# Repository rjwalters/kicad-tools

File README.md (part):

# kicad-tools

**Tools for AI agents to work with KiCad projects.**

🌐 **Live demo gallery: [kicad-tools.org](https://kicad-tools.org)** — explore example boards built end-to-end by these tools, with 2D/3D renders, routing & manufacturing metrics, downloadable fabrication packages, and an interactive in-browser PCB viewer.

This project provides standalone Python tools that enable AI agents (LLMs, autonomous coding assistants, etc.) to parse, analyze, and manipulate KiCad schematic and PCB files programmatically. All tools output machine-readable JSON and require no running KiCad instance.

## Why Agent-Focused?

Traditional EDA tools require GUIs and manual interaction. `kicad-tools` bridges the gap by providing:

- **Structured data access** - Parse KiCad files into clean Python objects
- **Machine-readable output** - Analysis and query commands offer JSON output; check each command’s `--help` for supported formats
- **Programmatic modification** - Edit schematics and PCBs without a GUI
- **LLM reasoning interface** - Purpose-built module for LLM-driven PCB layout decisions

Whether you're building an AI assistant that reviews PCB designs, automating DRC checks in CI, or experimenting with LLM-driven routing, these tools provide the foundation.

## Installation

```bash
# Base install (CPU only)
pip install kicad-tools

# With CUDA GPU acceleration (NVIDIA GPUs on Linux/Windows)
pip install kicad-tools[cuda]

# With Metal GPU acceleration (Apple Silicon Macs)
pip install kicad-tools[metal]

# With native C++ router backend
pip install kicad-tools[native]

# With CMA-ES placement optimization (kct optimize-placement / kct build --optimize-placement)
pip install kicad-tools[placement]

# Everything (all optional dependencies)
pip install kicad-tools[all]
```

> The `placement` extra pulls in `cmaes` (and, transitively, `scipy`). It is
> required by `kct optimize-placement` and the placement step of
> `kct build --optimize-placement`; without it those commands exit with a
> clear message naming the extra. The `dev` and `all` extras already include
> it, so `uv sync --extra dev` is sufficient for development.

To check GPU acceleration status:
```bash
kct calibrate --show-gpu
```

### In a board (consumer) repository

The supported setup for a PCB-design repo that depends on kicad-tools is **PyPI
plus a committed `uv.lock`**: `pyproject.toml` carries a lower bound
(`kicad-tools[<extras>]>=X`) and `uv.lock` is the exact pin. Install it, with
the agent skills, CI gates and conventions, from a kicad-tools checkout:

```bash
./scripts/install-kct.sh /path/to/board-repo        # PyPI floor (default; same as --pypi)
./scripts/install-kct.sh --upgrade-workflow /path/to/board-repo  # + weekly upgrade PR
cd /path/to/board-repo && uv lock && uv sync && uv run kct build-native
```

The installer keeps the repo's existing extras and removes any
`[tool.uv.sources]` kicad-tools entry. Re-running it is a no-op when the floor
is already current. `--upgrade-workflow` adds `.github/workflows/kct-upgrade.yml`,
which opens a PR for each new PyPI release; the PR raises the floor, refreshes
`uv.lock` and the vendored files, and lists the release's upgrade notes.
`kct doctor` checks that the vendored files match the installed version.

Git and SHA pins (`--tag vX.Y.Z`, `--rev <sha>`) and local checkouts
(`--path ../kicad-tools`) are escape hatches for short-lived use. If you need
a fix that is not on PyPI yet, ask for a patch release rather than carrying a
SHA pin. Run `./scripts/install-kct.sh --help` for every option.

## Quick Start

### Command Line (`kct`)

```bash
# List symbols in a schematic
kct symbols project.kicad_sch
kct symbols project.kicad_sch --format json

# Trace nets
kct nets project.kicad_sch
kct nets project.kicad_sch --net VCC

# Generate bill of materials
kct bom project.kicad_sch
kct bom project.kicad_sch --format csv --group

# Run ERC (requires kicad-cli)
kct erc project.kicad_sch
kct erc project.kicad_sch --errors-only

# Run DRC with manufacturer rules
kct drc board.kicad_pcb
kct drc board.kicad_pcb --mfr jlcpcb
kct mfr compare  # Compare manufacturer rules
```

### Python API

```python
from kicad_tools import load_schematic, Schematic

# Load and parse a schematic
doc = load_schematic("project.kicad_sch")
sch = Schematic(doc)

# Access symbols
for symbol in sch.symbols:
    print(f"{symbol.reference}: {symbol.value}")

# Access hierarchy
for sheet in sch.sheets:
    print(f"Sheet: {sheet.name}")
```

### PCB Autorouter

```python
from kicad_tools.router import Autorouter, DesignRules

# Configure design rules
rules = DesignRules(
    grid_resolution=0.25,  # mm
    trace_width=0.2,  # mm
    trace_clearance=0.15,  # mm
)

# Create router and add components
router = Autorouter(width=100, height=80, rules=rules)
router.add_component("U1", pads=[{"number": "1", "x": 10, "y": 10, "net": 1}])
router.add_component("U2", pads=[{"number": "1", "x": 20, "y": 10, "net": 1}])

# Route all nets
routes = router.route_all(timeout=30)
print(f"Created {len(routes)} routes")
```

### LLM-Driven PCB Layout

The reasoning module enables LLMs to make strategic PCB layout decisions while tools handle geometric execution:

```python
from kicad_tools import PCBReasoningAgent

# Load board
agent = PCBReasoningAgent.from_pcb("board.kicad_pcb")

# Reasoning loop
while not agent.is_complete():
    # Get state as prompt for LLM
    prompt = agent.get_prompt()

    # Call your LLM (OpenAI, Anthropic, local, etc.)
    command = call_llm(prompt)

    # Execute and get feedback
    result, diagnosis = agent.execute(command)

# Save result
agent.save("board_routed.kicad_pcb")
```

CLI usage:
```bash
# Export state for external LLM
kct reason board.kicad_pcb --export-state

# Interactive mode
kct reason board.kicad_pcb --interactive

# Auto-route priority nets
kct reason board.kicad_pcb --auto-route
```

See `examples/llm-routing/` for complete examples.

### MCP Server for AI Agents

Enable AI assistants like Claude to interact with KiCad designs via the Model Context Protocol:

```bash
# Install with MCP support
pip install "kicad-tools[mcp]"

# Run the MCP server
kct mcp serve
```

Register the server with your agent harness. `kct mcp setup` finds the
absolute `kct` path, merges into the existing config without touching other
servers, and is a no-op when re-run (`--dry-run` previews, `--format json` for
scripts):

```bash
kct mcp setup --client claude-code      # ~/.claude.json via `claude mcp add-json` (default; --scope project for ./.mcp.json)
kct mcp setup --client claude-desktop   # Claude Desktop config
kct mcp setup --client codex            # [mcp_servers.kct] in $CODEX_HOME/config.toml
kct mcp setup --client opencode         # ~/.config/opencode/opencode.json (--project for ./opencode.json)
```

Or configure Claude Desktop by hand (`~/Library/Application Support/Claude/claude_desktop_config.json`):

```json
{
  "mcpServers": {
    "kicad-tools": {
      "command": "python",
      "args": ["-m", "kicad_tools.mcp.server"]
    }
  }
}
```

Available MCP tools:
- **Analysis**: `board_summary`, `get_drc_violations`, `measure_clearance`
- **Export**: `export_gerbers`, `export_bom`, `export_assembly`
- **Placement**: `placement_analyze`, `placement_suggestions`
- **Sessions**: `start_session`, `query_move`, `apply_move`, `commit`, `rollback`
- **Routing**: `route_net`, `route_net_auto`, `get_unrouted_nets`
- **Optimization**: `optimize_placement`, `evaluate_placement`

See `docs/mcp/` for complete documentation.

### Circuit Blocks

Build schematics using reusable, tested circuit blocks:

```python
from kicad_tools.schematic.models import Schematic
from kicad_tools.schematic.blocks import (
    MCUBlock,
    CrystalOscillator,
    LDOBlock,
    USBConnector,
    DebugHeader,
    I2CPullups,
    ResetButton,
)

sch = Schematic("My STM32 Design")

# Add an MCU with bypass capacitors
mcu = MCUBlock(
    sch, x=150, y=100, part="STM32F103C8T6", bypass_caps=["100nF", "100nF", "100nF", "4.7uF"]
)

# Add crystal oscillator
xtal = CrystalOscillator(sch, x=100, y=100, frequency="8MHz", load_caps="20pF")

# Add power supply
ldo = LDOBlock(sch, x=50, y=100, input_voltage=5.0, output_voltage=3.3)

# Add USB connector with ESD protection
usb = USBConnector(sch, x=50, y=150, connector_type="type-c", esd_protection=True)

# Add debug header for programming
debug = DebugHeader(sch, x=200, y=100, interface="swd")

# Add I2C pull-ups
i2c = I2CPullups(sch, x=180, y=150, pullup_value="4.7k")

# Add reset button with debounce
reset = ResetButton(sch, x=120, y=50, debounce_cap="100nF")

# Connect via ports
sch.add_wire(ldo.port("VOUT"), mcu.port("VDD"))
sch.add_wire(xtal.port("OUT"), mcu.port("OSC_IN"))

sch.save()
```

Available blocks:
- **MCUBlock**: Microcontroller with bypass capacitors
- **CrystalOscillator**: Crystal/oscillator with load capacitors
- **LDOBlock**: Linear regulator with input/output capacitors
- **USBConnector**: USB-B/Mini/Micro/Type-C with optional ESD protection
- **DebugHeader**: SWD/JTAG/Tag-Connect programming headers
- **I2CPullups**: I2C bus pull-up resistors with optional filtering
- **ResetButton**: Reset switch with debounce capacitor
- **BarrelJackInput/USBPowerInput/BatteryInput**: Power input circuits
- **LEDIndicator**: Status LED with current-limiting resistor
- **DecouplingCaps**: Decoupling capacitor placement

See `boards/04-stm32-devboard/` for a complete design example.

### Project Workflow

Work with complete KiCad projects using the unified Project class:

```python
from kicad_tools import Project

# Load a KiCad project
project = Project.load("myboard.kicad_pro")

# Cross-reference schematic to PCB
result = project.cross_reference()
print(f"Unplaced components: {result.unplaced}")

# Export manufacturing files
project.export_assembly("output/", manufacturer="jlcpcb")
```

### Progress Callbacks

Monitor long-running operations with progress callbacks:

```python
from kicad_tools import ProgressCallback, ProgressContext
from kicad_tools.router import Autorouter

def on_progress(progress: float, message: str, cancelable: bool) -> bool:
    print(f"{progress * 100:.0f}%: {message}")
    return True  # Return False to cancel

# Use with context manager
with ProgressContext(on_progress):
    router = Autorouter(...)
    router.route_all()  # Progress reported automatically

# Or create JSON-formatted callbacks for automation
from kicad_tools import create_json_callback

callback = create_json_callback()
```

### Parametric Footprint Generators

Create KiCad footprints programmatically with IPC-7351 naming:

```python
from kicad_tools.library import create_soic, create_qfp, create_chip

# Generate SOIC-8 footprint
fp = create_soic(pins=8, pitch=1.27)
fp.save("SOIC-8.kicad_mod")

# Generate LQFP-48
fp = create_qfp(pins=48, pitch=0.5, body_size=7.0)
fp.save("LQFP-48.kicad_mod")

# Generate 0402 chip resistor
fp = create_chip("0402", prefix="R")
fp.save("R_0402.kicad_mod")
```

Available generators: `create_soic`, `create_qfp`, `create_qfn`, `create_sot`, `create_chip`, `create_dip`, `create_pin_header`.

### Symbol Library Management

Create and edit KiCad symbol libraries programmatically:

```python
from kicad_tools.schema.library import SymbolLibrary

# Create a new symbol library
lib = SymbolLibrary.create("myproject.kicad_sym")

# Create a symbol with pins
sym = lib.create_symbol("MyPart")
sym.add_pin("1", "VCC", "power_in", (0, 5.08))
sym.add_pin("2", "GND", "power_in", (0, -5.08))
sym.add_pin("3", "IN", "input", (-7.62, 0))
sym.add_pin("4", "OUT", "output", (7.62, 0))

# Save the library
lib.save()

# Load and edit existing library
lib = SymbolLibrary.load("existing.kicad_sym")
```

### Pure Python DRC

Run design rule checks without requiring kicad-cli:

```bash
# Check against manufacturer rules
kct check board.kicad_pcb --mfr jlcpcb --format json

# Check against a 4-layer rule set with 2 oz outer / 0.5 oz inner copper.
# (A scalar `--copper 2` would also apply 2 oz to inner layers; omit the flag
# when the board declares a stackup.)
kct check board.kicad_pcb --mfr jlcpcb --layers 4 --copper outer=2,inner=0.5
```

Python API:

```python
from kicad_tools.schema.pcb import PCB
from kicad_tools.validate import DRCChecker

pcb = PCB.load("board.kicad_pcb")
checker = DRCChecker(pcb, manufacturer="jlcpcb")
results = checker.check_all()

print(results.summary())
for violation in results:
    print(f"  {violation.rule_id}: {violation.message}")
```

### Placement Optimization

Optimize component placement using physics-based or evolutionary algorithms:

```python
from kicad_tools.optim import PlacementOptimizer, EvolutionaryPlacementOptimizer
from kicad_tools.schema.pcb import PCB

pcb = PCB.load("board.kicad_pcb")

# Physics-based optimization (force-directed)
optimizer = PlacementOptimizer.from_pcb(pcb)
optimizer.run(iterations=1000, dt=0.01)

# Get optimized placements
for comp in optimizer.components:
    print(f"{comp.ref}: ({comp.x:.2f}, {comp.y:.2f}) @ {comp.rotation:.1f}°")

# Evolutionary optimization (genetic algorithm)
evo = EvolutionaryPlacementOptimizer.from_pcb(pcb)
best = evo.optimize(generations=100, population_size=50)

# Hybrid: evolutionary global search + physics refinement
physics_opt = evo.optimize_hybrid(generations=50)
physics_opt.write_to_pcb(pcb)
pcb.save("optimized.kicad_pcb")
```

CLI usage:
```bash
kct placement optimize board.kicad_pcb --iterations 1000
```

### Trace Optimization

Optimize routed traces for shorter paths and fewer vias:

```python
from kicad_tools.router import TraceOptimizer
from kicad_tools.schema.pcb import PCB

pcb = PCB.load("board.kicad_pcb")
optimizer = TraceOptimizer(pcb)
optimizer.optimize()
pcb.save("optimized.kicad_pcb")
```

CLI usage:
```bash
kct optimize-traces board.kicad_pcb -o optimized.kicad_pcb
```

### Datasheet Tools

Search, download, and parse component datasheets:

```bash
# Search for datasheets
kct datasheet search STM32F103C8T6

# Download a datasheet
kct datasheet download STM32F103C8T6 -o datasheets/

# Convert PDF to markdown
kct datasheet convert datasheet.pdf -o datasheet.md

# Extract images and tables
kct datasheet extract-images datasheet.pdf -o images/
kct datasheet extract-tables datasheet.pdf
```

Python API:

```python
from kicad_tools.datasheet import DatasheetManager, DatasheetParser

# Search and download
manager = DatasheetManager()
results = manager.search("STM32F103C8T6")
datasheet = manager.download(results[0])

# Parse PDF
parser = DatasheetParser("STM32F103.pdf")
markdown = parser.to_markdown()

# Extract images and tables
images = parser.extract_images()
tables = parser.extract_tables()
for table in tables:
    print(table.to_markdown())
```

### Parts Lookup (LCSC / JLCPCB)

Look up LCSC part numbers, check BOM availability, and pull pricing/stock:

```python
from kicad_tools.parts import LCSCClient

client = LCSCClient()
part = client.lookup("C2040")
if part:
    print(f"{part.mfr_part}: {part.stock} in stock, best ${part.best_price:.4f}")
```

Part lookups resolve through a tiered chain (each tier falls back to the next):

1. **Local response cache** — previously fetched parts.
2. **Official JLCPCB open-platform API** — only when you supply your own API key
   (see below). Off by default; inert without keys.
3. **Anonymous scrape API** — the public JLCPCB web endpoints (requires the
   `parts` extra: `pip install "kicad-tools[parts]"`). **Note:** as of
   July 2026 JLCPCB's public endpoint returns 404 — treat this tier as
   best-effort/deprecated and rely on tier 2 (BYO key) or tier 4 (offline).
4. **Offline jlcparts catalog** — a locally synced mirror
   (`kct parts sync-catalog`, ~620 MB download, ~5 GB on disk, ~7.1 M
   components), usable fully offline.

#### Using your own JLCPCB API key

kicad-tools can talk to the **official JLCPCB open-platform API** using
credentials you register yourself at the JLCPCB developer portal
(<https://jlcpcb.com/> → developer/open platform). This is strictly opt-in: you
bring your own key, kicad-tools ships only the signed client. **Without keys,
behavior is unchanged** — the official tier is simply skipped.

Set all three environment variables (kicad-tools reads them via `os.environ`;
it does **not** load a `.env` file itself, so use your shell, `direnv`, or a
dotenv runner — see [`.env.example`](.env.example)):

```bash
export JLCPCB_APP_ID="your-app-id"
export JLCPCB_ACCESS_KEY="your-access-key"
export JLCPCB_SECRET_KEY="your-secret-key"
```

All three must be set (and non-empty) to activate the official tier; if any is
missing it stays inert. Once set, `LCSCClient.lookup()` / `lookup_many()` prefer
the official API for part-detail-by-code, falling back down the chain above on
any failure.

Notes and caveats:

- **What it unlocks:** authenticated *part detail lookup by LCSC code* only.
  There is **no confirmed official keyword/MPN search endpoint**, so
  `LCSCClient.search()` always uses the anonymous/offline path even with keys.
- **IP whitelisting:** the developer portal offers an IP-whitelist feature. If
  you enable it, your machine's public IP must be whitelisted or requests are
  rejected (surfaced as a distinct, actionable error).
- **Never commit credentials.** `.env` is gitignored; the secret key is used
  only as HMAC key material and is never transmitted.
- The request-signing scheme is not first-party-documented by JLCPCB; the client
  implements the best-available community-reverse-engineered variant for the
  Parts surface, with the two ambiguous parameters isolated as single
  flip-points in `parts/jlcpcb_api.py` (see that module and issue #4118).

## CLI Commands

### Unified CLI (`kct` or `kicad-tools`)

The commands below are the ones most workflows reach for. The authoritative
full list (every command and subcommand) lives in
[CLI Reference → Commands Overview](docs/reference/cli.md#commands-overview).

**Inspection and validation**

| Command | Description |
|---------|-------------|
| `kct symbols <schematic>` | List symbols with filtering |
| `kct nets <schematic>` | Trace and analyze nets |
| `kct bom <schematic>` | Generate bill of materials |
| `kct erc <schematic>` | Run electrical rules check |
| `kct drc <pcb>` | Run design rules check (requires kicad-cli) |
| `kct check <pcb>` | Pure Python DRC (no kicad-cli needed) |
| `kct creepage <pcb>` | HV surface-path (creepage) audit vs IEC 60664-1 / 62368-1 |
| `kct creepage-export-rules <project>` | Export voltage-domain netclasses + pairwise HV clearance rules so kicad-cli DRC enforces creepage |
| `kct analyze <pcb>` | Signal-integrity, current-sense, electrical-rating, and operating-state component-stress lint |
| `kct audit <project>` | Manufacturing readiness audit (ERC, DRC, connectivity, compatibility) |
| `kct impedance <subcommand>` | Transmission line impedance calculations |

**Layout and routing**

| Command | Description |
|---------|-------------|
| `kct route <pcb>` | Autoroute a PCB (`--nets`/`--skip-nets` to select nets, `--complete` to finish one) |
| `kct route-auto <pcb>` | Orchestrator-based multi-strategy autorouting |
| `kct optimize-traces <pcb>` | Optimize routed traces |
| `kct placement <pcb>` | Detect and optimize component placement |
| `kct optimize-placement <pcb>` | CMA-ES/Bayesian (`--strategy bayesian`, needs `kicad-tools[bayesian]`) global placement optimization |
| `kct zones <subcommand>` | Add copper pour zones (and `hv-keepout` plane voids) |
| `kct stitch <pcb>` | Auto-add stitching vias for plane connections |
| `kct reason <pcb>` | LLM-driven PCB layout reasoning |

**Repair**

| Command | Description |
|---------|-------------|
| `kct fix-drc <pcb>` | Automated DRC violation repair (clearance + drill + mask-copper) |
| `kct fix-erc <schematic>` | Automated ERC violation repair (PWR_FLAG + no-connect) |
| `kct fix-vias <pcb>` | Fix vias to meet manufacturer specifications (incl. off-pad relocation) |
| `kct pipeline <input>` | End-to-end repair pipeline for existing PCBs |

**Parts and manufacturing**

| Command | Description |
|---------|-------------|
| `kct datasheet <subcommand>` | Search, download, parse datasheets |
| `kct parts <subcommand>` | LCSC/JLCPCB part lookup, cache, offline catalog sync |
| `kct export <pcb>` | Manufacturing bundle export (gerbers, BOM, CPL) |
| `kct export-formats <pcb>` | PDF / SVG / STEP / IPC-2581 / ODB++ via kicad-cli, with a per-format result |
| `kct mfr <subcommand>` | Manufacturer rule profiles (apply-rules, validate) |
| `kct spec <subcommand>` | Project specification (`.kct`) management |
| `kct fleet status` | Routing + manufacturing readiness across all boards |

**Environment**

| Command | Description |
|---------|-------------|
| `kct doctor` | Diagnose kicad-tools installation health (version-record drift) |
| `kct build-native` | Build the C++ router backend for 10-100x faster routing |
| `kct mcp serve` | Start MCP server for AI agent integration |

Every `kct` subcommand that produces a result accepts `--format json` for
machine-readable output (some older commands also keep `--json` as a legacy
alias). A few commands are deliberately exempt -- e.g. `interactive`,
`mcp serve` and `run` -- see
[Machine Output](docs/reference/machine-output.md) for the inventory,
exemptions and per-command JSON shapes.

### PCB Tools

| Command | Description |
|---------|-------------|
| `kicad-pcb-query summary` | Board overview |
| `kicad-pcb-query footprints` | List footprints |
| `kicad-pcb-query nets` | List all nets |
| `kicad-pcb-query traces` | Trace statistics |
| `kicad-pcb-modify move` | Move component |
| `kicad-pcb-modify rotate` | Rotate component |

### Library Tools

| Command | Description |
|---------|-------------|
| `kicad-lib-symbols` | List symbols in library |

## Modules

| Module | Description |
|--------|-------------|
| `core` | S-expression parsing and file I/O |
| `schema` | Data models (Schematic, PCB, Symbol, Wire, Label) |
| `schematic.blocks` | Reusable circuit blocks (MCU, LDO, USB, debug headers, etc.) |
| `project` | Unified Project class for schematic+PCB workflows |
| `library` | Footprint generation and symbol library management |
| `drc` | Design Rule Check report parsing (kicad-cli output) |
| `validate` | Pure Python DRC checker (no kicad-cli needed) |
| `erc` | Electrical Rule Check report parsing |
| `manufacturers` | PCB fab profiles (JLCPCB, OSHPark, PCBWay, Seeed) |
| `operations` | Schematic operations (net tracing, symbol replacement) |
| `router` | A* PCB autorouter with trace optimization |
| `optim` | Placement optimization (physics-based, evolutionary) |
| `reasoning` | LLM-driven PCB layout with chain-of-thought reasoning |
| `progress` | Progress callbacks for long-running operations |
| `datasheet` | Datasheet search, download, and PDF parsing |
| `mcp` | MCP server for AI agent integration |
| `pcb.layout` | Layout preservation for PCB regeneration |

## What's New

Release notes live in [CHANGELOG.md](CHANGELOG.md) (one section per release,
newest first) and on the
[GitHub Releases page](https://github.com/2AMLogic/kicad-tools/releases).
Changes merged since the last release are collected as fragments under
[`changelog.d/`](changelog.d/) until the next release assembles them.

## Features

- **Pure Python parsing** - No KiCad installation needed
- **Round-trip editing** - Parse, modify, and save files preserving formatting
- **Full S-expression support** - Handles all KiCad 8.0+ file formats
- **Schematic analysis** - Symbols, wires, labels, hierarchy traversal
- **Circuit blocks** - Reusable blocks for MCU, power, USB, debug headers, I2C, reset
- **PCB analysis** - Footprints, nets, traces, vias, zones
- **Manufacturer rules** - JLCPCB, PCBWay, OSHPark, Seeed design rules
- **PCB autorouter** - A* pathfinding with net class awareness
- **Pure Python DRC** - Design rule checking without kicad-cli
- **Placement optimization** - Physics-based and evolutionary algorithms
- **Trace optimization** - Path shortening and via reduction
- **Footprint generation** - Parametric generators for common packages
- **Symbol library creation** - Programmatic symbol creation and editing
- **Datasheet tools** - Search, download, and PDF parsing
- **Progress callbacks** - Monitor and cancel long-running operations
- **JSON output** - Machine-readable output for automation

## Requirements

- Python 3.10+
- numpy (for router module)
- KiCad 8+ (optional) - for running ERC/DRC via `kicad-cli`

## Development

This project uses [uv](https://docs.astral.sh/uv/) for fast, reproducible Python environment management.

### Quick Start

```bash
# Clone repository
git clone https://github.com/2AMLogic/kicad-tools.git
cd kicad-tools

# Set up development environment (installs all dev dependencies)
uv sync --extra dev

# Build the C++ router backend (REQUIRED for production routing speed,
# delivers 10-100x A* speedup vs pure-Python; takes ~30s on first build,
# cached thereafter). uv sync does NOT build this — fresh checkouts and
# fresh worktrees need this step explicitly.
uv run kct build-native

# Verify the C++ backend is installed
uv run kct build-native --check
# Expected: "C++ backend: available (version 1.0.0)"

# Run tests
uv run pytest

# Run linter
uv run ruff check .

# Format code
uv run ruff format .
```

> **Routing performance note**: Without the C++ backend, board routing falls
> back to pure-Python A* — typically 5-10x slower per net, which can push
> medium boards (e.g. board 07 in `boards/07-matchgroup-test/`) past the
> default 6-minute CI cap. If `kct route` appears stuck or per-net log lines
> take tens of seconds, run `kct build-native --check` first — a missing
> extension is the most common cause.

#### Fresh worktree checklist

> Pinned renders and `kct pcb model-audit --env pinned` also need the
> checksum-verified KiCad 3D model subset: run `uv run kct models sync --sparse`
> once (about 14 MB; cached under `~/.cache/kicad-tools/kicad-3dmodels/`). Without
> it they report `pinned model set not synced`; nothing else breaks.

1. **Sync the lock-pinned dev environment first**:

   ```bash
   uv sync --frozen --extra dev
   ```

   A fresh worktree performs no Python env setup, and a stale or drifted
   `.venv/` (e.g. a mypy newer than the `uv.lock` pin) produces spurious
   mypy-baseline noise that looks like real type regressions (issue #4558).
   `--frozen` guarantees the resolved set matches `uv.lock` exactly — the
   same environment CI uses. Loom-created worktrees run this automatically
   via the `.loom/hooks/post-worktree.sh` hook; run it manually for
   hand-made worktrees or if the hook reported a failure.

2. **Build the native extension.** The worktree's `.venv/` does not inherit
   the C++ extension built in the main checkout, and `uv sync` does not
   build it. After `cd` into the worktree, run `uv run kct build-native`
   once before any routing benchmarks.

3. **If a local `mypy` error names a file outside your diff, `rm -rf .mypy_cache` and re-run before investigating it.** `.mypy_cache/` is
   gitignored, so it survives `git reset --hard`, `git clean -fd`, a rebase,
   and a worktree reuse — bare `mypy` / `pnpm typecheck` can replay an error
   computed against an older tree. CI is always cold (no `actions/cache`), so
   it will not reproduce the phantom. `scripts/ci/check_mypy_baseline.py` is
   already immune (it runs `--no-incremental`); see
   [`docs/contributing/development.md`](docs/contributing/development.md#the-stale-mypy_cache-trap).

4. **Know where kicad-cli's library tables come from before trusting native
   ERC/DRC results.** kicad-cli resolves stock nicknames (`Resistor_SMD:`)
   through the *global* `fp-lib-table`/`sym-lib-table` in its config home,
   which the GUI writes on first launch -- or never, on a fresh host, CI
   container or `docker run --user 0:0`. Without them every stock footprint
   becomes a `lib_footprint_issues` DRC warning and every stock symbol an ERC
   warning that reads like a real defect (issues #5860, #6962; board 03 once
   gained 37 of them). The library configuration is part of the pinned
   toolchain, not of the host:

   - **Where it comes from.** `src/kicad_tools/data/kicad-config/10.0/` holds
     flat copies of the stock tables shipped in CI's pinned image (CI's
     `KICAD_IMAGE` digest in `.github/workflows/ci.yml`).
   - **How producers isolate it.** Every evidence producer (`kct readiness`,
     `scripts/boards/refresh_readiness.py`, the `scripts/boards/regenerate_*`
     scripts) and every KiCad CI job runs kicad-cli with a scratch
     `KICAD_CONFIG_HOME` holding exactly those tables, and never reads or
     writes your GUI config. kct's Docker fallback (`KCT_KICAD_DOCKER=1`)
     runs the same pinned digest, not the floating `kicad/kicad:10.0` tag.
   - **Native evidence needs the pinned toolchain.** Producers refuse (exit 2,
     nothing written) a kicad-cli other than the image's release (10.0.6), and
     refuse any DRC report with `lib_footprint_issues`. On a host with another
     KiCad release, route kicad-cli through the image:
     `KCT_KICAD_DOCKER=1 uv run kct readiness boards/<board> --verify --checked-at <ISO>`.
     A fixed `--checked-at` makes two runs byte-identical.
   - **How to check it.**

     ```bash
     uv run python -m kicad_tools.cli.kicad_toolchain --check            # host kicad-cli
     KCT_KICAD_DOCKER=1 uv run python -m kicad_tools.cli.kicad_toolchain --check
     ```

   For ad-hoc `kct check` runs outside a producer, point the current shell
   at the pinned tables (CI's container jobs do this in their "Initialize
   stock KiCad libraries" step):

   ```bash
   eval "$(python3 scripts/ci/init_kicad_libraries.py --shell)"
   ```

The build's `nanobind` dependency is composed into the default dev
dependency-group, so a plain `uv sync` keeps it resolved and a later
`uv sync` (e.g. adding `--extra placement`) will not prune it. If you
installed with only a subset of groups, add the `native` extra explicitly
so nanobind stays lockfile-tracked:

```bash
uv sync --extra native            # repo/dev worktree
pip install "kicad-tools[native]" # consumer / installed wheel
```

Avoid a bare `pip install nanobind` — it is not recorded in the resolved
set and a subsequent `uv sync` will uninstall it, breaking the next
`kct build-native` (issue #4412).

**Opening a PR from a fork?** Fork PRs run on GitHub-hosted runners rather than
this project's self-hosted one, which makes the `Test` job roughly 2.2x slower
(~50 min, with a 90-minute budget). Nothing is skipped and nothing extra is
required of you — see
[`docs/contributing/development.md`](docs/contributing/development.md#6-what-to-expect-from-ci-on-a-fork-pr)
for the details and the maintainer fallback if a run still cannot finish.

### Available Commands

If you have `pnpm` installed, you can use these convenience scripts:

| Command | Description |
|---------|-------------|
| `pnpm setup` | Set up dev environment (`uv sync --extra dev`) |
| `pnpm test` | Run tests |
| `pnpm test:cov` | Run tests with coverage |
| `pnpm test:benchmark` | Run performance benchmarks |
| `pnpm lint` | Check code with ruff |
| `pnpm lint:fix` | Auto-fix lint issues |
| `pnpm format` | Format code with ruff |
| `pnpm format:check` | Check formatting |
| `pnpm typecheck` | Run mypy type checking |
| `pnpm check:ci` | Run full CI suite (format + lint + tests) |

### Direct uv Commands

```bash
# Run tests with coverage
uv run pytest --cov=kicad_tools --cov-report=term-missing

# Run benchmarks
uv run pytest tests/test_benchmarks.py --benchmark-only

# Type checking
uv run mypy src/

# Full CI check
uv run ruff format . --check && uv run ruff check . && uv run pytest
```

## Agent Skills (`kct` namespace)

kicad-tools ships its own Claude agent skills under `.claude/commands/kct/` (invoked as `/kct:<name>`), a harness-agnostic namespace kept separate from any installed orchestration framework. Nine skills ship today — `/kct:tapeout` (complete fab-ready export bundle or loud refusal), `/kct:manufacturing-readiness` (sign-off gates), `/kct:hv-isolation-loop` (mains/HV creepage design loop), `/kct:board-recipe-scaffold`, `/kct:layout-journal`, `/kct:ee-review` (advisory EE decision document for analog/placement-blocked boards), `/kct:circuit-review` (schematic-vs-datasheet review before layout), `/kct:submit-jlcpcb` (JLCPCB PCBA submission prep from a signed-off tapeout bundle; orders only through an opt-in, attended checkout leg the operator runs for a total they approve exactly), and `/kct:help` (introspective guide to the namespace). See [.claude/commands/kct/README.md](.claude/commands/kct/README.md) for the full contracts. The skill text is harness-neutral; [docs/agent-surfaces.md](docs/agent-surfaces.md) lists what each skill needs from Claude Code, Codex CLI or opencode.

The skills ship inside the `kicad-tools` wheel (`kicad_tools/agent_skills/kct/`), so a plain `pip install kicad-tools` is enough; no clone of this repository is needed. Install them with `kct skills install`:

```bash
kct skills install                       # ./.claude/commands/kct/*.md (Claude Code, project)
kct skills install --user                # ~/.claude/commands/kct/
kct skills install --target /tmp/x       # /tmp/x/kct/*.md
kct skills install --harness codex       # ./.agents/skills/kct-<name>/SKILL.md
kct skills install --harness opencode    # ./.opencode/commands/kct/*.md, run as /kct/<name>
kct skills install --list                # packaged skills and their install state
kct skills install --check               # exit 1 if the installed copy has drifted
```

Re-running is idempotent. `--prune` removes `kct` skill files the package no longer ships, and `--dry-run` previews. Edit skills in `src/kicad_tools/agent_skills/kct/`; `.claude/commands/kct/` is a synced copy (`uv run python scripts/sync_agent_skills.py --write`).

## Using kicad-tools from Claude Code, Codex and opencode

Each harness needs two setup commands: one registers the MCP server, the other
installs the `kct` skills in that harness's own format. The skill sources are
shared, so every harness gets the same skills.

| Harness | MCP server | Skills | Invoke a skill |
|---|---|---|---|
| Claude Code | `kct mcp setup --client claude-code` | `kct skills install` (`.claude/commands/kct/`) | `/kct:<name>`, e.g. `/kct:tapeout <board-path>` |
| Codex CLI | `kct mcp setup --client codex` | `kct skills install --harness codex` (`.agents/skills/kct-<name>/`) | Codex skills: `$kct-<name>`, e.g. `$kct-tapeout <board-path>` |
| opencode | `kct mcp setup --client opencode` | `kct skills install --harness opencode` once opencode rendering lands (#5951) | `/kct/<name>` |

Add `--user` to `kct skills install` to install for every project. Then start
the agent with the primer:

```bash
kct agent-guide                   # workflow, JSON contract, sign-off rule, pitfalls
kct agent-guide --harness codex   # with skill examples in Codex syntax
kct agent-guide --format json     # {"version", "harness", "sections": [...]}
```

`kct agent-guide` ships in the wheel and reads the same in every harness. Point
your agent at it from `CLAUDE.md` or `AGENTS.md` instead of copying it.

## Related Projects

<!-- BEGIN kct:ecosystem -->

kicad-tools is one piece of a fast-moving KiCad automation ecosystem. This
section is generated from `src/kicad_tools/ecosystem/data/projects.toml` --
run `kct ecosystem where-we-sit` for our invariants and non-goals, `kct
ecosystem show <id>` for any entry below, and see [docs/ecosystem.md](docs/ecosystem.md)
for the full positioning narrative. Where we have evaluated a project in
depth, the linked note carries the method, the measurements and the verdict,
including the cases where the other tool wins.

Licenses are the SPDX id from the upstream `LICENSE` file, and are
load-bearing: an AGPL or unlicensed neighbour is studied at the capability
level only, never copied from. Facts below were last verified on the date each
registry entry records; `.github/workflows/ecosystem-drift.yml` re-checks them
weekly.

### Autorouters

- **[KiCadRoutingTools](https://github.com/drandyhaas/KiCadRoutingTools)** (MIT, Python + Rust, 488★) -- **Benchmarked against us.** The closest peer to `kct route`: octilinear multi-layer A\* with via insertion, diff pairs, length matching, BGA/QFN fanout and plane pours, shipped as both a KiCad 9/10 action plugin and a CLI. Benchmarked head-to-head against us on eight demo boards under one shared `kicad-cli` referee: it is faster and completes more nets on the sparse and medium boards, while on the dense boards it emits literal shorts where we instead run out of time. Our evaluation: [docs/research/kicad-routing-tools-comparison.md](docs/research/kicad-routing-tools-comparison.md).
- **[TraceMaker](https://github.com/DingoOz/TraceMaker)** (GPL-3.0-or-later, C++20 + CUDA, 42★) -- **Benchmarked against us.** C++20/CUDA KiCad 9/10 router that reads and writes `.kicad_pcb` directly and is judged by `kicad-cli` DRC. Octilinear-lattice A\* with exact legality checks, negotiated rip-up, an 8-variant deterministic portfolio under a `--work` budget, min-cost-flow escape-corridor reservation, a nogood cache, coupled diff-pair search, and a SQLite bandit that learns which variant to pick across runs; the GPU only accelerates cost fields. On PCBWorld D3 the circuit-skills author reports 0.99 / 1.00 / 0.90 clean on the small / medium / large splits, against about 0.7 / 0.7 / 0.2 for Freerouting 2.2.4 -- third-party, single 60 s runs, not reproduced by us, and on PCBench boards TraceMaker was developed against (its own held-out figure is 73-78% clean). Its "clean" also excludes DRC errors already in the input board, looser than our 0-DRC bar. Days old; copyleft, so ideas only, and run only as an external binary. Our evaluations: [docs/research/kct-route-escape-flow-experiment.md](docs/research/kct-route-escape-flow-experiment.md), [benchmarks/external/fleet_routers/verdict.md](benchmarks/external/fleet_routers/verdict.md).
- **[freerouting](https://github.com/freerouting/freerouting)** (GPL-3.0, Java, 2068★) -- the long-standing Specctra DSN/SES autorouter and the baseline most KiCad users try first. Has a headless CLI, but the DSN round-trip is a lossy interchange boundary: it routes a translated view of the board rather than the `.kicad_pcb` itself. We operate on the board file directly, which is what lets LVS and the manufacturing gates run against the same artifact that gets fabricated. PCBWorld's paper reports it as the strongest published rule-based baseline on real boards (Clean Pass 0.80 / 0.78 on D3-A / D3-B). fastroute is a faster Rust port of it with a byte-identical parity mode.
- **[OrthoRoute](https://github.com/bbenchoff/OrthoRoute)** (MIT, Python + CUDA/Metal, 411★) -- GPU-accelerated PathFinder routing, with plugin and headless modes. Its author is explicit that it targets a narrow class of very large, dense, highly regular multilayer backplanes and BGA escape patterns and does poorly on typical boards -- the opposite end of the board-size spectrum from our demo fleet.
- **[DeepPCB KiCad plugin](https://github.com/instadeepai/deeppcb-kicad-plugin)** (Apache-2.0, Python, 66★) -- **Evaluated and not adopted.** An open-source plugin in front of a closed, credit-metered cloud router. The plugin is local; the routing is not. It requires an account and API key, so it cannot participate in an offline or air-gapped CI pipeline. DeepPCB's own published benchmark numbers are recorded in `benchmarks/external/boards.toml` for side-by-side comparison. Our evaluations: [benchmarks/external/README.md](benchmarks/external/README.md), [benchmarks/external/results/report.md](benchmarks/external/results/report.md).
- **[tscircuit autorouter](https://github.com/tscircuit/tscircuit-autorouter)** (MIT, TypeScript, 85★) -- **Benchmarked against us.** Tscircuit's built-in router (`@tscircuit/capacity-autorouter`): a pipeline of hypergraph / successive-approximation solvers rather than net-by-net A\*, fed a `SimpleRouteJson` problem instead of a KiCad file. It ships a public benchmark (`dataset-srj18`, derived from real Arduino and Antmicro KiCad boards) and a bug-report-to-fixture workflow. Partly benchmarked against us (Arduino Nano only): SRJ drops netclass width, clearance, zones and keepouts, so its completion is not comparable. Our evaluation: [docs/research/tscircuit-evaluation.md](docs/research/tscircuit-evaluation.md).
- **[WeaveEngine](https://github.com/c28ba/WeaveEngine)** (GPL-3.0-or-later, Python, 71★) -- **Ideas adopted.** Topology-first DSN/SES autorouter: a planar embedding of all nets is chosen jointly before any geometry (which side of every pad and placed trace each connection passes, so crossings are unrepresentable by construction), then traces are drawn as taut clearance-bound curves. The triangulate-and-string-pull half is one we already ship (mesh router, #4267); the transferable delta is the global ordering step -- joint candidate selection, airwire-separation and severance costs, regret ordering -- which our evaluation (#8993) turned into follow-up issues against the epic #5509 ordering class. No diff pairs, length matching, impedance or net-class priority; pours delegated to KiCad; vias are its own documented weak subsystem. Our evaluation: [docs/research/weaveengine-topology-first-evaluation.md](docs/research/weaveengine-topology-first-evaluation.md).

### Design as code (upstream of us)

- **[atopile](https://github.com/atopile/atopile)** (MIT, Python, 3964★) -- **Ideas adopted.** A language and compiler for describing boards as code (`.ato`), with constraint solving, a package registry and parametric part selection via its Faebryk library; it emits a netlist and updates a KiCad layout, but deliberately stops at "place and route in KiCad". That is exactly where we start, which makes the two complementary rather than competing. Our MCP server exists because of this evaluation. Our evaluations: [docs/research/atopile-research-synthesis.md](docs/research/atopile-research-synthesis.md), [docs/research/faebryk-component-library.md](docs/research/faebryk-component-library.md), [docs/research/atopile-constraint-solving.md](docs/research/atopile-constraint-solving.md), [docs/research/atopile-interface-patterns.md](docs/research/atopile-interface-patterns.md), [docs/research/atopile-layout-reuse.md](docs/research/atopile-layout-reuse.md), [docs/research/atopile-lsp-analysis.md](docs/research/atopile-lsp-analysis.md), [docs/research/atopile-mcp-analysis.md](docs/research/atopile-mcp-analysis.md), [docs/research/atopile-package-registry.md](docs/research/atopile-package-registry.md), [docs/research/atopile-error-handling.md](docs/research/atopile-error-handling.md).
- **[SKiDL](https://github.com/devbisme/skidl)** (MIT, Python, 1675★) -- the original Python-as-schematic-capture tool: a program describes the circuit and SKiDL emits netlists, XML BOMs and (for KiCad 6-10) editable schematics, with its own ERC. Another upstream producer of the files we consume.
- **[tscircuit](https://github.com/tscircuit/tscircuit)** (MIT, TypeScript, 2776★) -- **Evaluated and not adopted.** "React for Electronics" -- circuits described in TypeScript/React and compiled to its own Circuit JSON. Its `circuit-json-to-kicad` converter emits `.kicad_sch`, `.kicad_pcb` (with traces, vias and pours) and `.kicad_pro`, and `kicad-to-circuit-json` reads them back, so it is an upstream producer of the files we consume, like atopile and SKiDL. **Gated and not yet usable as a front end**: five representative designs were run through `kct check --mfr`, LVS and `kicad-cli pcb drc --refill-zones`, before and after re-routing with `kct route`, and all five failed. The blocking defect is that its schematic and PCB converters name the same net differently, so no emitted project can pass LVS at all; vias, netclass and silkscreen defaults also sit below every mainstream fab floor. Our parser reads the files without complaint, and `kct route` produced opens where tscircuit's own autorouter produced shorts. Six upstream defects were recorded with reproducers and re-verified on upstream HEAD (2026-10-18): three confirmed and tracked upstream, two fixed or covered upstream, one not a bug. The relation stays upstream/complementary. Our evaluation: [docs/research/tscircuit-evaluation.md](docs/research/tscircuit-evaluation.md).
- **[component-importer-for-kicad](https://github.com/robertxdx/component-importer-for-kicad)** (MIT, Python, 55★) -- **Evaluated and not adopted.** Evaluated as a vendor-ZIP (SnapEDA / Ultra Librarian) ingestion backend for symbol and footprint import. Verdict was borrow-with-refactor rather than vendor: its headless modules are PyQt6-free and close to the surface we need, but a clean-room re-implementation of roughly 600 LoC plus a `kct ingest-zip` CLI is the smaller change. Not built yet. Our evaluation: [docs/research/component-importer-for-kicad-evaluation.md](docs/research/component-importer-for-kicad-evaluation.md).

### Agent and MCP interfaces

- **[Zeo](https://github.com/zeodotdev/zeo)** (AGPL-3.0, C++, 31★) -- a KiCad fork with an integrated AI agent sidebar and MCP server. Takes a complementary approach: live editor manipulation via IPC vs. our offline file-based analysis and optimization.
- **[Konnect](https://github.com/mixelpixx/Konnect)** (AGPL-3.0, Rust, 1424★) -- **Ideas adopted.** Upstream was archived on 2026-10-26 (read-only, no further releases expected); it continues as Konnect-EDA (Orchis-ai-LLC), which is commercial closed-source software, so there is no source left to audit and no further capability audits are planned. The open replacement is our own clean-room openkonnect, with Konnect-EDA as the closed-source successor. The ideas we adopted stand on their own, and KiCAD-MCP-Server is now our agent-interface reference. A single-binary native KiCad 10 plugin exposing a very large LLM tool surface (228 tools in 21 toolsets) across schematic, layout, routing, placement, review and manufacturing. AGPL means no code can move between it and this MIT repo in either direction, so our engagement is capability-level only: we audited its connectivity primitives, its tool-economy design and its design-rule handling against our own surface. Five of its six connectivity primitives we already had; the sixth (near-miss auto-snap repair) was a real gap. Re-checked at v0.13: four new ideas adopted as follow-ups (visual baselines, truth-contract audit, honest-schema CI guard, SES provenance). Our evaluations: [docs/research/konnect-connectivity-audit.md](docs/research/konnect-connectivity-audit.md), [docs/konnect-item1-toolset-economy-audit.md](docs/konnect-item1-toolset-economy-audit.md), [docs/konnect-item8-design-rules-audit.md](docs/konnect-item8-design-rules-audit.md), [docs/research/konnect-v013-delta.md](docs/research/konnect-v013-delta.md).
- **[copperhead](https://github.com/copperheadhq/copperhead)** (Apache-2.0, TypeScript, 312★) -- **Ideas adopted.** "cursor for circuit boards": a natural-language brief drives direct edits to `.kicad_sch` / `.kicad_pcb`, gated by an LLM-free `check` and wrapped in a git snapshot that auto-rolls-back on failure. It does not route, and verifies with `kicad-cli` ERC/DRC only -- no LVS, no manufacturing cross-gate. Its *process* design (design memory as committed artifacts, a constraints registry, a per-run audit trail) is the part worth borrowing. Note: moved from `chouhanindustries/copperhead` since our note was written. Our evaluation: [docs/research/copperhead-workflow-ideas.md](docs/research/copperhead-workflow-ideas.md).
- **[Seeed-Studio/kicad-mcp-server](https://github.com/Seeed-Studio/kicad-mcp-server)** (no `LICENSE` committed, Python, 135★) -- the closest peer to `kct mcp serve`: an MCP server that reads schematic and PCB files offline (shelling out to `kicad-cli` for validation) to trace pin-level connections and edit designs. Overlaps our read/analyze tools; carries no router, LVS or fab-readiness gates. Its README claims MIT but the repo commits no LICENSE file, so we treat it as all-rights-reserved and copy nothing.
- **[circuit-skills](https://github.com/punkfab/circuit-skills)** (no `LICENSE` committed, Python, 9★) -- Claude Code skills for code-driven electronics: ngspice/Falstad circuit simulation, a tscircuit-placement -> KiCad IPC (`kipy`) route-and-DRC loop, board/enclosure fit co-design and 3D renders. Its `route_eval` harness now runs five routing backends on any KiCad board (two Freerouting versions, TraceMaker, the tscircuit router, and an experimental `srj-legal` that has TraceMaker re-route what KiCad's DRC rejects in tscircuit output) and keeps the best, with an optional fastroute backend and a PCBWorld D3 harness; it self-reports 0.98 Clean Pass on D3-A for `srj-legal`, unreproduced by us. Overlaps our `/kct:*` skills, but still assumes the tail is hand-finished in KiCad -- the opposite of our fully automated bar. No LICENSE committed, so ideas only; mining tracked in issue #5886. Our evaluations: [docs/research/circuit-skills-evaluation.md](docs/research/circuit-skills-evaluation.md), [docs/research/placement_score_calibration.md](docs/research/placement_score_calibration.md).
- **[Backplane](https://github.com/BackplaneWorks/Backplane)** (MIT, Bend + TypeScript, 430★) -- an agentic KiCad/FreeCAD hub: Claude Code, Codex and others work on a local project while board, schematic and 3D viewers redraw each save in a browser, phone or desktop app. It snapshots the KiCad files after every tool call onto a hidden git ref (private index, never the user's) and compares any two versions as a uuid-keyed removed/changed/added board diff -- geometric only, no DRC or LVS. Agents get the exact `kicad-cli`, the canonical files and the KiStack skills. Its board diff is the idea we lacked for reviewing routing PRs (#6417). Note: moved from `i2cjak/Backplane` since our note was written. Our evaluation: [docs/research/backplane-kistack-evaluation.md](docs/research/backplane-kistack-evaluation.md).
- **[KiStack](https://github.com/BackplaneWorks/kistack)** (MIT, Markdown (agent skills), 397★) -- **Evaluated and not adopted.** Ten human-written KiCad agent skills (553 lines of prose) for schematics, symbols (KLC), footprints (kicad-library-tools), layout, BOM, exports, Gerber review, panelizing and product renders; Backplane and kicadmium both ship it. Overlaps our `/kct:*` skills, but its layout skill tells agents to route by hand and avoid autorouters -- the opposite of our fully automated bar. Our evaluation: [docs/research/backplane-kistack-evaluation.md](docs/research/backplane-kistack-evaluation.md).
- **[KiCAD-MCP-Server](https://github.com/mixelpixx/KiCAD-MCP-Server)** (MIT, Python + TypeScript, 2978★) -- actively developed again (pushed 2026-10-26) and now our agent-interface reference in place of the archived Konnect. The most-starred KiCad MCP server: ~250 fine-grained tools for project setup, schematic and board editing, Freerouting, DRC/ERC, export, symbol and footprint creation and JLCPCB parts lookup. It is the MIT predecessor of Konnect. Compared tool-by-tool with `kct mcp serve` (pinned 628d320f): a wide imperative editing surface against our narrow session/verification one, so complementary; parts alternatives, symbol library writes and schematic cosmetic lint are worth borrowing under MIT with attribution. Its Freerouting runner is not: we improve our own router rather than add a fallback (#7991). Our evaluation: [docs/research/kicad-mcp-server-evaluation.md](docs/research/kicad-mcp-server-evaluation.md).

### Fabrication and CI

- **[KiBot](https://github.com/INTI-CMNB/KiBot)** (AGPL-3.0, Python, 747★) -- the mature, scriptable fabrication- and documentation-output generator for KiCad (gerbers, drill, position, BOM, 3D, plots), with a GitHub Action. Deeper than `kct export` on output *variety* and configuration; it assumes a board that is already routed and signed off, which is the part we automate.

### KiCad bindings

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
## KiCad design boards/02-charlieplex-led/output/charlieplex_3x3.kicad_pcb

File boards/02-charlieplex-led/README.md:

# ATtiny85 Charlieplex LED Grid

A working 3 × 3 red LED sequencer built around a real ATtiny85-20PU. Four GPIO pins drive nine LEDs through four 330 Ω resistors. The 50 × 55 mm, two-layer board includes regulated 3.3–5 V power input, supply decoupling, reset pullup, and a standard six-pin AVR ISP header.

See [HARDWARE.md](HARDWARE.md) for the complete pinout, verified component identities, power instructions and firmware programming. U1, J1 and J2 are through-hole parts listed in the CPL and BOM for fab assembly (procurement review). The supplied firmware advances through D1–D9; physical hardware testing has not yet been performed.

## Rebuild

From the repository root, with KiCad and the project Python environment installed:

```sh
uv run python boards/02-charlieplex-led/generate_design.py /tmp/charlieplex-rebuild
```

The schematic and PCB generators share `hardware_design.py` and `design_spec.py`. Native library footprints preserve the actual DIP and header geometry. The deterministic routing recipe traces all twelve nets, then `finalize_routing.py` applies reviewed escape-via corrections, raises silkscreen widths to the fabrication minimum, and requires native KiCad DRC to have zero findings. These explicit corrections address router defects; they do not suppress checks.

`output/manufacturing.zip` contains the fabrication and assembly package. Its manifest records the package files and SHA256 hashes. `output/readiness.json` records current validation evidence and input hashes.

## Charlieplexing

Each LED connects between two GPIO nodes. To light it, one GPIO drives high, another drives low, and the other two remain inputs without pullups. Four GPIOs can address twelve directed pairs; this board populates nine. The current path contains two 330 Ω resistors, yielding about 4.5 mA with a 5 V supply and a 2 V LED drop. The firmware blanks the matrix before changing direction to avoid ghosting.

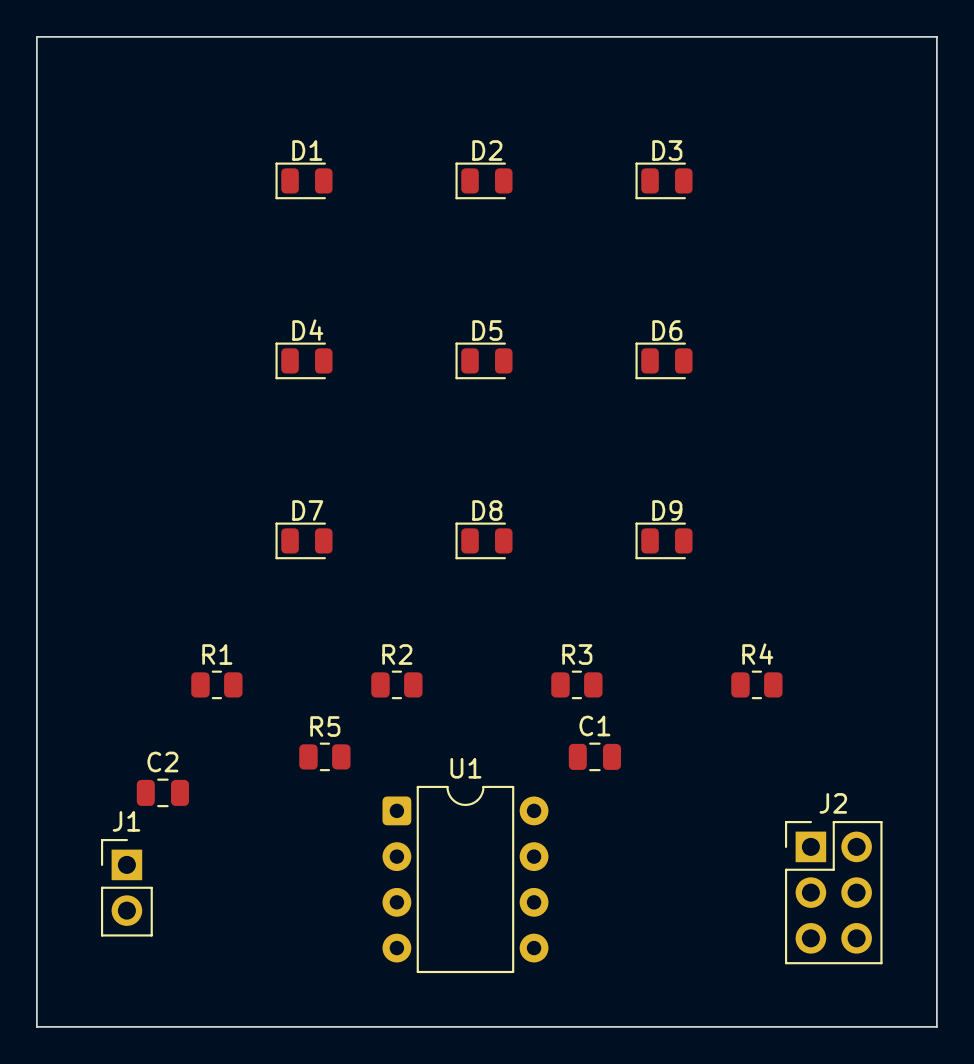
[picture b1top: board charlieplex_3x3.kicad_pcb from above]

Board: 2 copper layers, 50.0 x 55.0 mm, 19 parts (0 on the bottom side), 12 nets, no tracks yet.

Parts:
C1: 100nF; C_0805_2012Metric
C2: 4.7uF; C_0805_2012Metric
D1, D2, D3, D4, D5, D6, D7, D8, D9: LED; LED_0805_2012Metric
J1: POWER; PinHeader_1x02_P2.54mm_Vertical
J2: AVR-ISP; PinHeader_2x03_P2.54mm_Vertical
R1, R2, R3, R4: 330R; R_0805_2012Metric
R5: 10k; R_0805_2012Metric
U1: ATtiny85-20PU; DIP-8_W7.62mm

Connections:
GND: C1.2, C2.2, J1.2, J2.6, U1.4 (GND)
ISP_SCK: J2.3, U1.7 (PB2)
LINE_A: R1.1, U1.2 (XTAL1/PB3)
LINE_B: R2.1, U1.3 (XTAL2/PB4)
LINE_C: J2.4, R3.1, U1.5 (AREF/PB0)
LINE_D: J2.1, R4.1, U1.6 (PB1)
NODE_A: D1.2 (A), D2.1 (K), D3.2 (A), D4.1 (K), D5.2 (A), D6.1 (K), R1.2
NODE_B: D1.1 (K), D2.2 (A), D7.2 (A), D8.1 (K), D9.2 (A), R2.2
NODE_C: D3.1 (K), D4.2 (A), D7.1 (K), D8.2 (A), R3.2
NODE_D: D5.1 (K), D6.2 (A), D9.1 (K), R4.2
RESET: J2.5, R5.2, U1.1 (~RESET/PB5)
VCC: C1.1, C2.1, J1.1, J2.2, R5.1, U1.8 (VCC)

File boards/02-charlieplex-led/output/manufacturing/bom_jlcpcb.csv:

Comment,Designator,Footprint,LCSC Part #
100nF,C1,Capacitor_SMD:C_0805_2012Metric,C49678
10k,R5,Resistor_SMD:R_0805_2012Metric,C17414
330R,"R1,R2,R3,R4",Resistor_SMD:R_0805_2012Metric,C17630
4.7uF,C2,Capacitor_SMD:C_0805_2012Metric,C1779
ATtiny85-20PU,U1,Package_DIP:DIP-8_W7.62mm,C965497
AVR-ISP,J2,Connector_PinHeader_2.54mm:PinHeader_2x03_P2.54mm_Vertical,C65114
LED,"D1,D2,D3,D4,D5,D6,D7,D8,D9",LED_SMD:LED_0805_2012Metric,C131244
POWER,J1,Connector_PinHeader_2.54mm:PinHeader_1x02_P2.54mm_Vertical,C7501260

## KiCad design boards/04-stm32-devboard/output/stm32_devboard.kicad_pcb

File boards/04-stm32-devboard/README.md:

# End-to-End PCB Design Example

This example demonstrates the complete workflow for creating a PCB design programmatically using kicad-tools.

The reviewed assembled design uses **MCP1825S-3302E/DB (C148031)**; do not
substitute AMS1117, whose pinout differs. Order two layers with the **paid
0.15mm mechanical drilling option** and tented through vias. Eight drill
positions were moved clear of SMT lands. See [DESIGN_REVIEW.md](DESIGN_REVIEW.md)
for the manufacturer evidence, power limits, and first-article checks.
Current fabrication/assembly evidence is hash-bound in `output/readiness.json`;
the full reviewed package is `output/manufacturing.zip`.

## Quick Start

```bash
# One-command build (recommended)
kct build boards/04-stm32-devboard

# Or run specific steps
kct build boards/04-stm32-devboard --step schematic

# Preview what would happen
kct build boards/04-stm32-devboard --dry-run
```

## Overview

We create a simple **STM32 Development Board** (Blue Pill style) with both
schematic and a fully-placed PCB:

- 5V → 3.3V LDO voltage regulator (MCP1825S-3302E/DB) with input/output decoupling
- **STM32F103C8T6 MCU** (LQFP-48, 0.5mm pitch) -- placed and wired:
  - PA13/PA14 → SWDIO/SWCLK
  - PB3       → SWO
  - PD0/PD1   → OSC_IN/OSC_OUT (HSE crystal)
  - PB12      → USER_LED (active-low)
  - NRST      → SWD reset pin
  - BOOT0     → 10k pull-down (R2) for flash boot
  - VDD/VDDA/VBAT → +3.3V; VSS/VSSA → GND
  - Bypass: C12-C15 (100nF per VDD pin) + C16 (4.7uF bulk)
- 8MHz HSE crystal Y1 with 20pF load caps C10/C11
- 6-pin SWD debug header J1 (+3.3V, SWDIO, SWCLK, SWO, NRST, GND)
- User LED D1 with 330R series resistor R1 (active-low on PB12)

## Circuit Blocks Used

| Block | Purpose | Components Created |
|-------|---------|-------------------|
| `LDOBlock` | 5V to 3.3V voltage regulation | U1, C1-C3 |
| `CrystalOscillator` | 8MHz HSE crystal with load caps | Y1, C10-C11 |
| `DebugHeader` | SWD programming interface | J1 |
| `LEDIndicator` | User LED with current-limiting resistor | D1, R1 |

## Advanced: Manual Build

For more control, run the Python script directly:

```bash
# From repository root
uv run python boards/04-stm32-devboard/generate_design.py

# Or specify output directory
uv run python boards/04-stm32-devboard/generate_design.py /path/to/output
```

## Output Files

The script generates:

```
output/
├── stm32_devboard.kicad_pro          # KiCad project file
├── stm32_devboard.kicad_sch          # Schematic
├── stm32_devboard.kicad_pcb          # Unrouted PCB with all footprints placed
└── stm32_devboard_routed.kicad_pcb   # Auto-routed PCB
```

Open the schematic in KiCad to view and continue the design.

## Manufacturing readiness status

The current readiness state lives in `output/readiness.json` (hash-bound to
the committed files, including any recorded `known_issues`). To see it:

```bash
uv run kct fleet status --boards-dir boards/04-stm32-devboard
```

This README does not repeat it, so it cannot go stale.

## Schematic Layout

```
    +5V ─────────────────────────────────────────────────────────
                    │
                    │
    USB-C ──────────┴───── LDO ──────┬───── MCU ───── Debug Header
     J1                    U1        │       U2          J2
                                     │
    +3.3V ───────────────────────────┴───────────────────────────
                                                    │
                                    Crystal         LED
                                      Y1           D1
                                       │            │
    GND ─────────────────────────────────────────────────────────
```

## Code Walkthrough

### 1. Create Schematic

```python
from kicad_tools.schematic.models.schematic import Schematic

sch = Schematic(
    title="STM32F103C8 Development Board",
    date="2025-01",
    revision="A",
)
```

### 2. Add Power Input

```python
from kicad_tools.schematic.blocks import USBConnector

usb = USBConnector(
    sch,
    x=30,
    y=100,
    connector_type="type-c",
    esd_protection=True,
)
```

### 3. Add Voltage Regulator

```python
from kicad_tools.schematic.blocks import LDOBlock

ldo = LDOBlock(
    sch,
    x=80,
    y=100,
    ref="U1",
    value="MCP1825S-3302E/DB",
    input_cap="10uF",
    output_caps=["10uF", "100nF"],
)

# Connect to power rails
ldo.connect_to_rails(
    vin_rail_y=30,  # 5V rail
    vout_rail_y=50,  # 3.3V rail
    gnd_rail_y=200,  # Ground rail
)
```

### 4. Add Crystal Oscillator

```python
from kicad_tools.schematic.blocks import CrystalOscillator

xtal = CrystalOscillator(
    sch,
    x=250,
    y=60,
    frequency="8MHz",
    load_caps="20pF",
)
```

### 5. Add Debug Header

```python
from kicad_tools.schematic.blocks import DebugHeader

debug = DebugHeader(
    sch,
    x=280,
    y=140,
    interface="swd",
    pins=6,
)
```

### 6. Add User LED

```python
from kicad_tools.schematic.blocks import LEDIndicator

led = LEDIndicator(
    sch,
    x=300,
    y=100,
    ref_prefix="D1",
    label="USER",
    resistor_value="330R",
)
```

### 7. Write Output

```python
sch.write("output/stm32_devboard.kicad_sch")
```

## Available Circuit Blocks

The `kicad_tools.schematic.blocks` module provides these reusable blocks:

### Power
- `LDOBlock` - LDO regulator with input/output capacitors
- `USBConnector` - USB Type-C/Micro-B/Mini-B with ESD protection
- `USBPowerInput` - USB power input with fuse protection
- `BarrelJackInput` - Barrel jack with reverse polarity protection
- `BatteryInput` - Battery connector with protection

### Oscillators
- `OscillatorBlock` - Active oscillator with decoupling
- `CrystalOscillator` - Passive crystal with load capacitors

### Passive Components
- `LEDIndicator` - LED with current-limiting resistor
- `DecouplingCaps` - Bank of decoupling capacitors

### MCU Support
- `MCUBlock` - MCU with bypass capacitors on power pins
- `DebugHeader` - SWD/JTAG/Tag-Connect debug interfaces

## Next Steps

The generator already builds a complete schematic + placed PCB and runs the
auto-router.  After generating, you can:

1. **Open in KiCad** - inspect the schematic and PCB visually
2. **Run ERC** - `kct erc boards/04-stm32-devboard/output/stm32_devboard.kicad_sch`
3. **Run DRC** - `kct check boards/04-stm32-devboard/output/stm32_devboard.kicad_pcb --mfr jlcpcb`
4. **Re-route** - `kct route boards/04-stm32-devboard/output/stm32_devboard.kicad_pcb -o ./routed.kicad_pcb --timeout 240`
5. **Export Files** - generate Gerbers, BOM, and CPL via `kct export`

## Project API

The `Project` API supports routing and manufacturing exports for an existing
project (see `src/kicad_tools/project.py`):

```python
from kicad_tools import Project

project = Project.load("output/stm32_devboard.kicad_pro")

# Auto-route with the default routing rules.
project.route()

# Export Gerbers and the assembly package (including BOM and positions).
project.export_gerbers("output/manufacturing/", manufacturer="jlcpcb")
project.export_assembly("output/manufacturing/", manufacturer="jlcpcb")
```

`project.check_drc(manufacturer="jlcpcb", layers=2, report_path=...)`
checks an existing native KiCad DRC report; generate that report first.
Schematic-to-PCB synchronization still uses the CLI workflow above;
`project.sync_to_pcb()` is not implemented.

## Related Examples

- [examples/01-schematic-analysis](../../examples/01-schematic-analysis/) - Parse existing schematics
- [examples/02-bom-generation](../../examples/02-bom-generation/) - Extract BOM from designs
- [examples/03-drc-checking](../../examples/03-drc-checking/) - Validate against manufacturer rules
- [examples/04-autorouter](../../examples/04-autorouter/) - PCB autorouting strategies

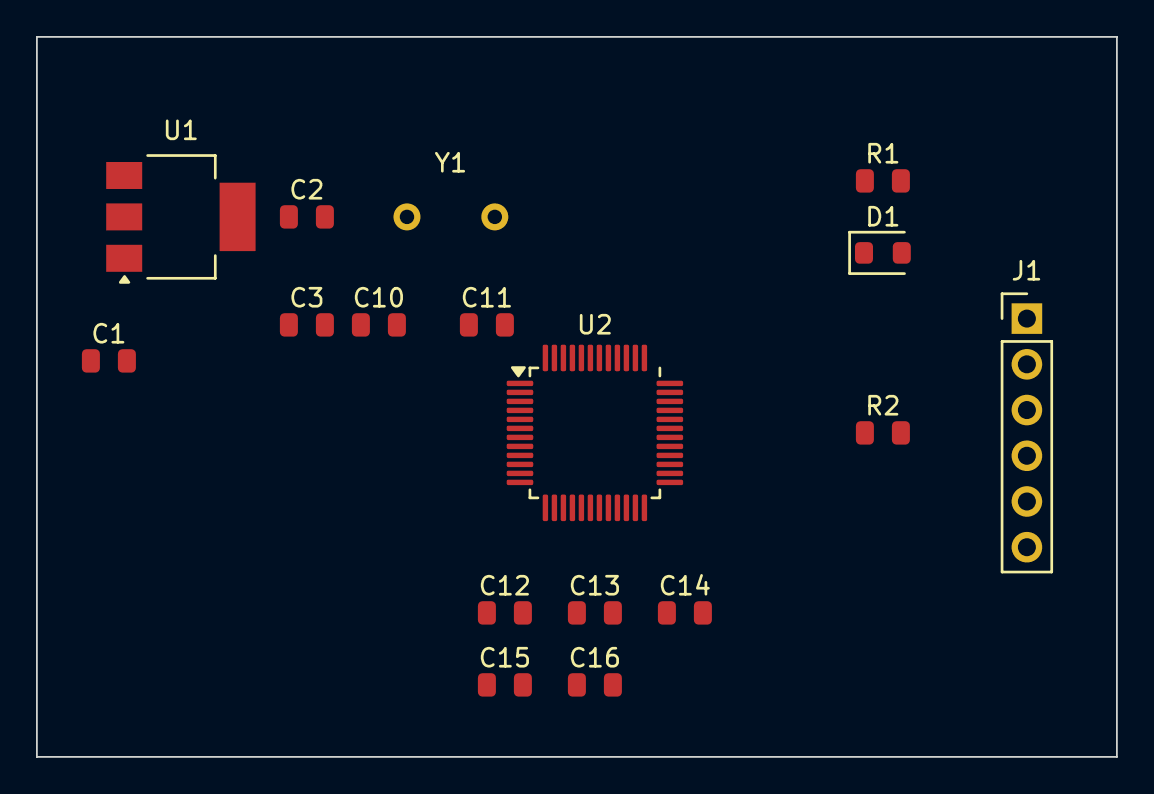
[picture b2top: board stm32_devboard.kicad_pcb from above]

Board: 2 copper layers, 60.0 x 40.0 mm, 17 parts (0 on the bottom side), 12 nets, no tracks yet.

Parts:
C1, C2: 10uF; C_0805_2012Metric
C3, C12, C13, C14, C15: 100nF; C_0805_2012Metric
C10, C11: 20pF; C_0805_2012Metric
C16: 4.7uF; C_0805_2012Metric
D1: LED; LED_0805_2012Metric
J1: SWD-6; PinHeader_1x06_P2.54mm_Vertical
R1: 330R; R_0805_2012Metric
R2: 10k; R_0805_2012Metric
U1: MCP1825S-3302E/DB; SOT-223-3_TabPin2
U2: STM32F103C8T6; LQFP-48_7x7mm_P0.5mm
Y1: 8MHz; Crystal_HC49-4H_Vertical

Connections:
+3.3V: C2.1, C3.1, C12.1, C13.1, C14.1, C15.1, C16.1, J1.1, R1.1, U1.3 (VO), U2.1 (VBAT), U2.9 (VDDA), U2.24 (VDD), U2.36 (VDD), U2.48 (VDD)
+5V: C1.1, U1.1 (VI)
BOOT0: R2.1, U2.44 (BOOT0)
GND: C1.2, C2.2, C3.2, C10.2, C11.2, C12.2, C13.2, C14.2, C15.2, C16.2, J1.6, R2.2, U1.2 (GND), U2.8 (VSSA), U2.23 (VSS), U2.35 (VSS), U2.47 (VSS)
LED_K: D1.1 (K), R1.2
NRST: J1.5, U2.7 (NRST)
OSC_IN: C10.1, U2.5 (PD0), Y1.1
OSC_OUT: C11.1, U2.6 (PD1), Y1.2
SWCLK: J1.3, U2.37 (PA14)
SWDIO: J1.2, U2.34 (PA13)
SWO: J1.4, U2.39 (PB3)
USER_LED: D1.2 (A), U2.25 (PB12)

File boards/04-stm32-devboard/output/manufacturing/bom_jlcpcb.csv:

Comment,Designator,Footprint,LCSC Part #
100nF,"C12,C13,C14,C15,C3",Capacitor_SMD:C_0805_2012Metric,C49678
10k,R2,Resistor_SMD:R_0805_2012Metric,C17414
10uF,"C1,C2",Capacitor_SMD:C_0805_2012Metric,C15850
20pF,"C10,C11",Capacitor_SMD:C_0805_2012Metric,C1798
330R,R1,Resistor_SMD:R_0805_2012Metric,C17630
4.7uF,C16,Capacitor_SMD:C_0805_2012Metric,C1779
8MHz,Y1,Crystal:Crystal_HC49-4H_Vertical,C114147
LED,D1,LED_SMD:LED_0805_2012Metric,C131244
MCP1825S-3302E/DB,U1,Package_TO_SOT_SMD:SOT-223-3_TabPin2,C148031
STM32F103C8T6,U2,Package_QFP:LQFP-48_7x7mm_P0.5mm,C8734
SWD-6,J1,Connector_PinHeader_2.54mm:PinHeader_1x06_P2.54mm_Vertical,C37208

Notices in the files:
README.md:
License: MIT
- **[easyeda2kicad](https://github.com/uPesy/easyeda2kicad.py)** (AGPL-3.0, Python, 1714★) -- **Ideas adopted.** EasyEDA/LCSC to KiCad converter (symbol, footprint, 3D model), v1.0.1 at our read.
- **[kicad-library-tools](https://gitlab.com/kicad/libraries/kicad-library-tools)** (GPL-3.0-or-later, Python (CadQuery), 80★) -- headless CadQuery generators for KiCad's official 3D packages (DIP, chip R/C/L, diodes, crystals, connectors, QFN/QFP/BGA, terminal blocks).
No LICENSE: all rights reserved, ideas only.
